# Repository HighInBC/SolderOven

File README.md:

# SolderOven
A control board to turn a toaster oven and a relay into a solder oven

While this is a public project I am not planning on documenting it until it is somewhat ready.

Consider this to be at the pre-alpha development stage. Things **DO NOT WORK** yet.

##Purpose

The purpose of this board is to act as a solder oven control board.
In addition to providing a user interface it will use a relay to control a toaster oven to provide the functionality of a solder oven.

##Features

Not all of these features are functional yet.

###Microcontroller

An ATMEGA328P-AU sits at the heart of the device controlling all of the other components.

###I2C display

Using an I2C port for an external display will allow a wide variety of choices that can be implemented in firmware

###Rotary encoder

A rotary encoder with a push button will be the primary source of user interaction.

###RGB LED

A ws2812b LED will be able to switch to any color or brightness to act as an indicator.

###Buzzer

A small piezo buzzer is used to make audio signals to the user

###Reset button

To reset the unit

###Serial port

The serial port can be used to reprogram the device.
It features an auto reset circuit on the DTR line to mimic the behaviour of an arduino nano but with an external FTDI bpard.

When not being used for programming the port can be used for peripherals such as a wifi bridge or sd card logger.

###Thermocouple sensor

A MAX6675 is used to read and digitize the signal from a type-k thermocouple. Two female 4mm banana plug sockets are on the board for easy connection. This is used to monitor the temperature of the oven.

###External temperature sensor

A port to attach one or more DS18B20 temperature sensors is available. This is used to monitor the temperature of the relay and its housing, further sensors can be added as it is a 1-wire protocol. Has a built in 4.7K pull-up resistor on the data pin for the 1-wire interface.

###Relay output

A port to attach the logic side of a relay to. It is expected that the relay takes a 5V logic level signal and does its own current limiting under 40mA. If your relay needs more than that then you need to add a suitable transistor.

##Associated datasheets

* [ATMEGA382P-AU](http://www.atmel.com/images/Atmel-8271-8-bit-AVR-Microcontroller-ATmega48A-48PA-88A-88PA-168A-168PA-328-328P_datasheet_Complete.pdf)
* [WS2812B](https://cdn-shop.adafruit.com/datasheets/WS2812B.pdf)
* [MAX6675](https://datasheets.maximintegrated.com/en/ds/MAX6675.pdf)
* [DS18B20](https://datasheets.maximintegrated.com/en/ds/DS18B20.pdf)
* [S8050](http://www.gangyi.com.cn/UploadFiles/2007828165749876.pdf)

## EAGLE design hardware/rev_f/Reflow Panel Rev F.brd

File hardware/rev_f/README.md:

Warning, this board revision has faults. Do not order.

Ordered from OSHPark for testing on 2016-08-05

Received and assembled August 8th, 2016. Results:

The following hardware features work correctly:

- ATMEGA328P-AU MCU
- Auto-program over serial port arduino nano style using external FTDI board
- WS2812B LED
- Buzzer
- Thermocouple reading
- Rotary encoder/button
- Reset button
- I2C display
- Relay ouput
- Power input

Errors on board:

- Mounting holes are too crowded and too close to the edges. Have to expand board size
- The DS18B20 is attached to ADC6, this port is only for analog reading and cannot control the port. Next revision has this moved to PD5

Added a bodge wire from PD5 to the DS18B20 data line. Works correctly.

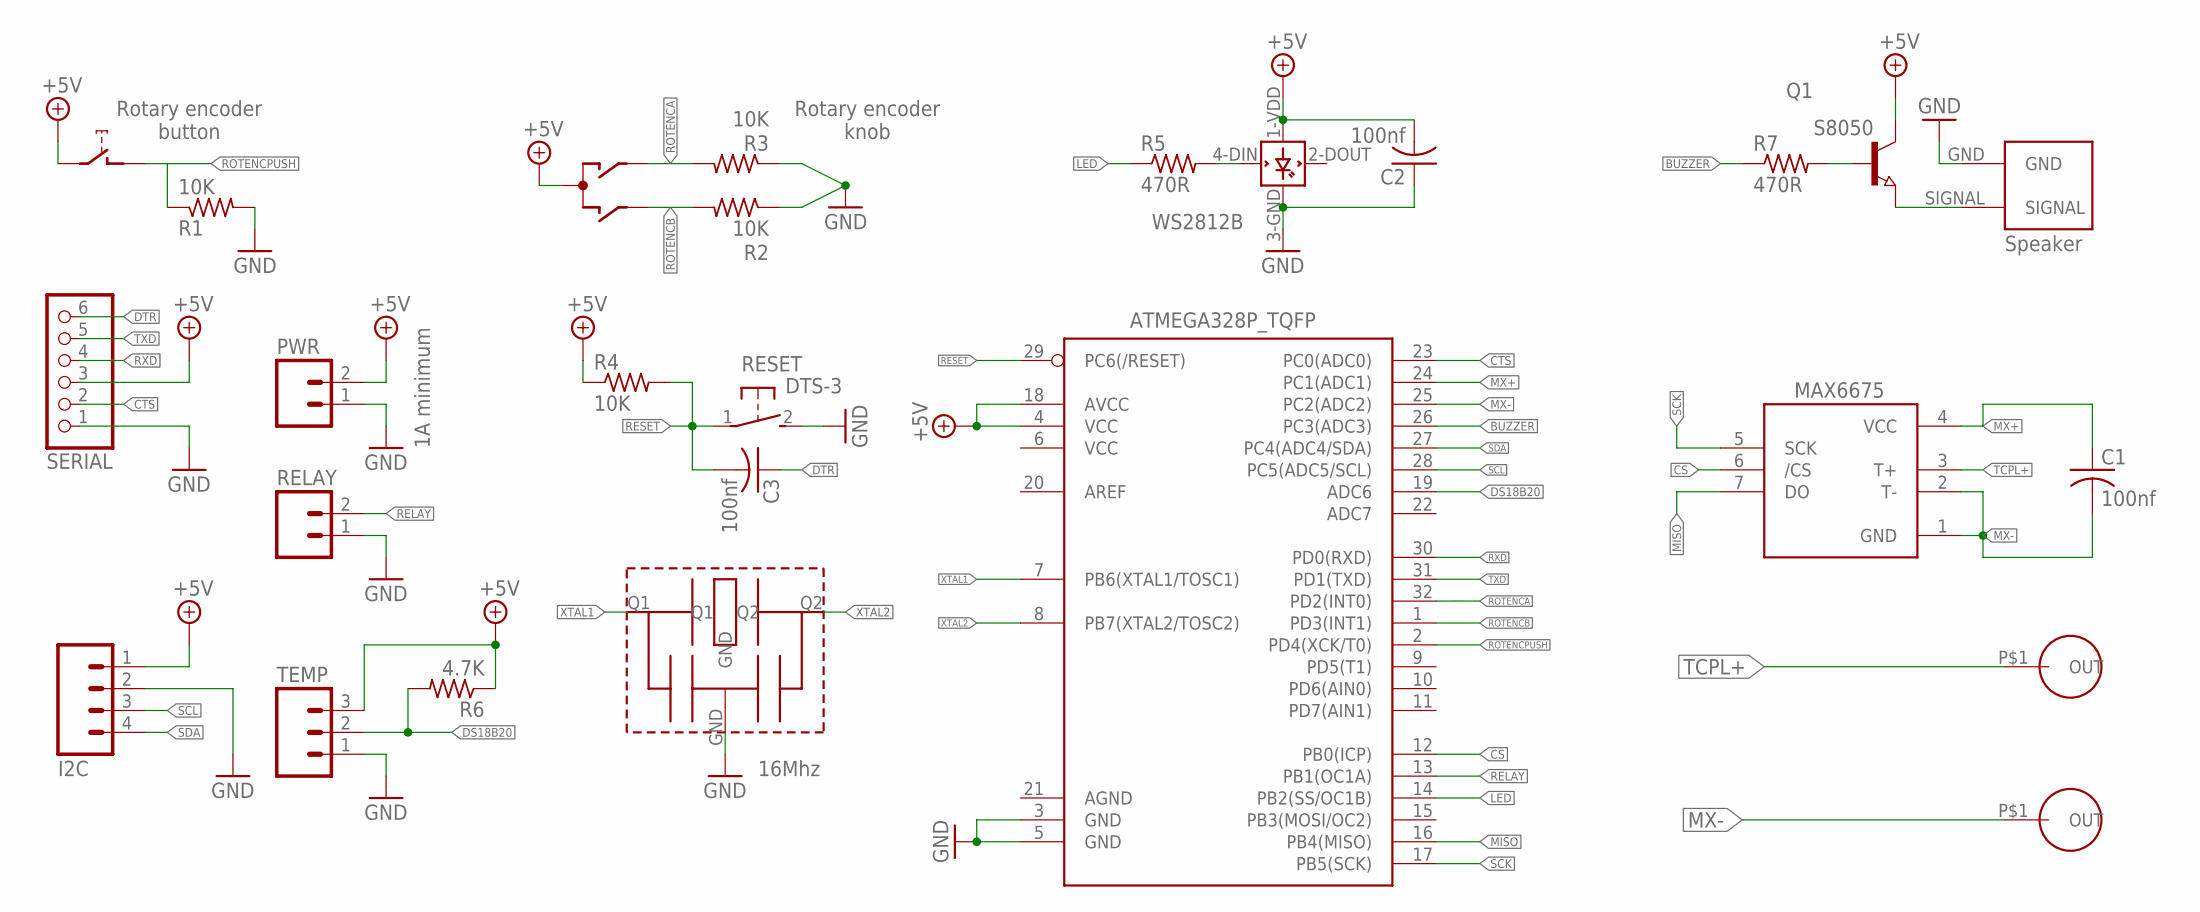
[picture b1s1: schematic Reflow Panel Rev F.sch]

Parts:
C1, C2, C3: 100nf; C0805
I2C: M04LOCK_LONGPADS; 1X04_LOCK_LONGPADS
IC2: MAX6675; SO08
L1: WS2812B_; WS2812B
PWR: M02LOCK; 1X02_LOCK
Q1: NPN-TRANSISTOR_SOT23; SOT23
R1, R2, R3, R4: 10K; M0805
R5, R7: 470R; M0805
R6: 4.7K; M0805
RELAY: M02LOCK; 1X02_LOCK
RESET: DTS-3
SERIAL: PINHD-1X6LOCK; 1X06-BIGLOCK
SW1: EC12E_SW; ALPS_EC12E_SW
TEMP: M03LOCK; 1X03_LOCK
U1: ATMEGA328P_TQFP; TQFP32-08
U$1: 8.5MMSQUAREBUZZER
U$2: CSTCE16M0V53-R0; CSTCE_V13C
U$3, U$4: BANANAFEMAIL-10.8-5.7; BANANAFEMALE-10.8-5.7

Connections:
+5V: C2.2, I2C.1, L1.1-VDD (VDD), PWR.2, Q1.3 (C), R4.1, R6.1, SERIAL.3, SW1.C, SW1.E (2), TEMP.3, U1.4 (VCC), U1.18 (AVCC)
BUZZER: R7.1, U1.26 (PC3(ADC3))
CS: IC2.6 (/CS), U1.12 (PB0(ICP))
CTS: SERIAL.2, U1.23 (PC0(ADC0))
DS18B20: R6.2, TEMP.2, U1.19 (ADC6)
DTR: C3.1, SERIAL.6
GND: C2.1, I2C.2, L1.3-GND (GND), PWR.1, R1.2, R2.1, R3.1, RELAY.1, RESET.2, SERIAL.1, TEMP.1, U1.3 (GND), U1.5 (GND), U$1.GND, U$2.GND
LED: R5.1, U1.14 (PB2(SS/OC1B))
MISO: IC2.7 (DO), U1.16 (PB4(MISO))
MX+: C1.1, IC2.4 (VCC), U1.24 (PC1(ADC1))
MX-: C1.2, IC2.1 (GND), IC2.2 (T-), U1.25 (PC2(ADC2)), U$3.P$1
unnamed: L1.4-DIN (DIN), R5.2
unnamed: Q1.2 (E), U$1.SIGNAL
unnamed: Q1.1 (B), R7.2
RELAY: RELAY.2, U1.13 (PB1(OC1A))
RESET: C3.2, R4.2, RESET.1, U1.29 (PC6(/RESET))
ROTENCA: R3.2, SW1.A, U1.32 (PD2(INT0))
ROTENCB: R2.2, SW1.B, U1.1 (PD3(INT1))
ROTENCPUSH: R1.1, SW1.D (1), U1.2 (PD4(XCK/T0))
RXD: SERIAL.4, U1.30 (PD0(RXD))
SCK: IC2.5 (SCK), U1.17 (PB5(SCK))
SCL: I2C.3, U1.28 (PC5(ADC5/SCL))
SDA: I2C.4, U1.27 (PC4(ADC4/SDA))
TCPL+: IC2.3 (T+), U$4.P$1
TXD: SERIAL.5, U1.31 (PD1(TXD))
XTAL1: U1.7 (PB6(XTAL1/TOSC1)), U$2.Q1
XTAL2: U1.8 (PB7(XTAL2/TOSC2)), U$2.Q2

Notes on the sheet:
Speaker
S8050
WS2812B
Rotary encoder button
Rotary encoder knob
16Mhz
1A minimum

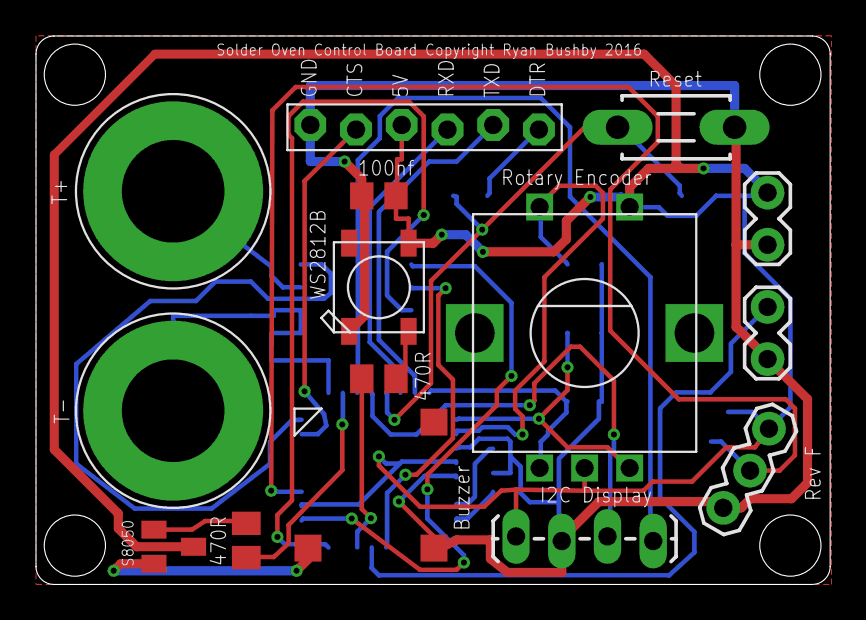
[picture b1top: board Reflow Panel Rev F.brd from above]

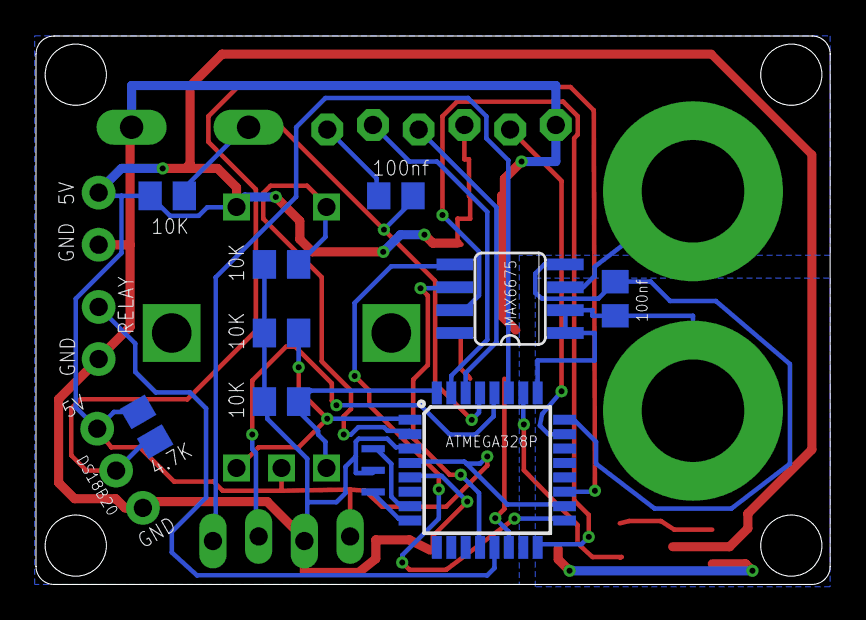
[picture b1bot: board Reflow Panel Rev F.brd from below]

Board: 2 copper layers, 44.1 x 30.5 mm, 25 parts (10 on the bottom side), 27 nets.

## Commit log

2016-07-28 Note about unreadiness of software
2016-07-29 Adding current state of design
2016-07-29 Purpose
2016-07-29 Adding planned feature list
2016-07-29 Corrections
2016-07-29 remove irrelevant info, add specific current limit
2016-07-29 typo
2016-07-29 info about pull up
2016-07-29 about relay control pin limits
2016-07-31 organize folders
2016-07-31 prior boards ordered
2016-08-05 silkscreen mod, order update
2016-08-09 Adding datasheet links
2016-08-21 Results of testing Rev F
2016-08-21 Update warning
2016-08-21 format
2016-08-21 finicky markdown
2016-08-21 Update on bodge test
2016-08-23 Adding bodge
2016-08-23 replacing
2016-08-23 replacement
2016-08-23 scaled
2016-08-23 add image of repair
2016-08-23 replace

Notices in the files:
hardware/rev_f/Reflow Panel Rev F.brd:
Solder Oven Control Board Copyright Ryan Bushby 2016
parts and their libraries:
User-Submitted: Licensing: Creative Commons ShareAlike 4.0 International - https://creativecommons.org/licenses/by-sa/4.0
